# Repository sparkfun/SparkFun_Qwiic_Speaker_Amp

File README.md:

SparkFun Qwiic Speaker Amp
========================================

[*SparkFun Qwiic Speaker Amp - TPA2016D2 (DEV-20690)*](https://www.sparkfun.com/products/20690)

A Qwiic-enabled breakout board for the Texas Instruments TPA2016D2 2.8W Class-D stereo audio amp.

Repository Contents
-------------------

* **/Documentation** - Datasheets, additional product information
* **/Hardware** - Eagle design files (.brd, .sch)
  * **/Production** - Production panel files (.brd)

Documentation
--------------

* **[Installing an Arduino Library Guide](https://learn.sparkfun.com/tutorials/installing-an-arduino-library)** - Basic information on how to install an Arduino library.
* **[Library](https://github.com/sparkfun/SparkFun_TPA2016D2_Arduino_Library)** - Arduino library for the Qwiic Speaker Amp.
* **[Hookup Guide](https://learn.sparkfun.com/tutorials/2749)** - Basic hookup guide for the Qwiic Speaker Amp.

Product Versions
----------------

* **[DEV-20690](https://www.sparkfun.com/products/20690)** - Initial release

Version History
---------------
* v1.0 - Initial release

License Information
-------------------

This product is _**open source**_! 

Please review the LICENSE.md file for license information. 

If you have any questions or concerns on licensing, please contact technical support on our [SparkFun forums](https://forum.sparkfun.com/viewforum.php?f=152).

Distributed as-is; no warranty is given.

- Your friends at SparkFun.

_<COLLABORATION CREDIT>_

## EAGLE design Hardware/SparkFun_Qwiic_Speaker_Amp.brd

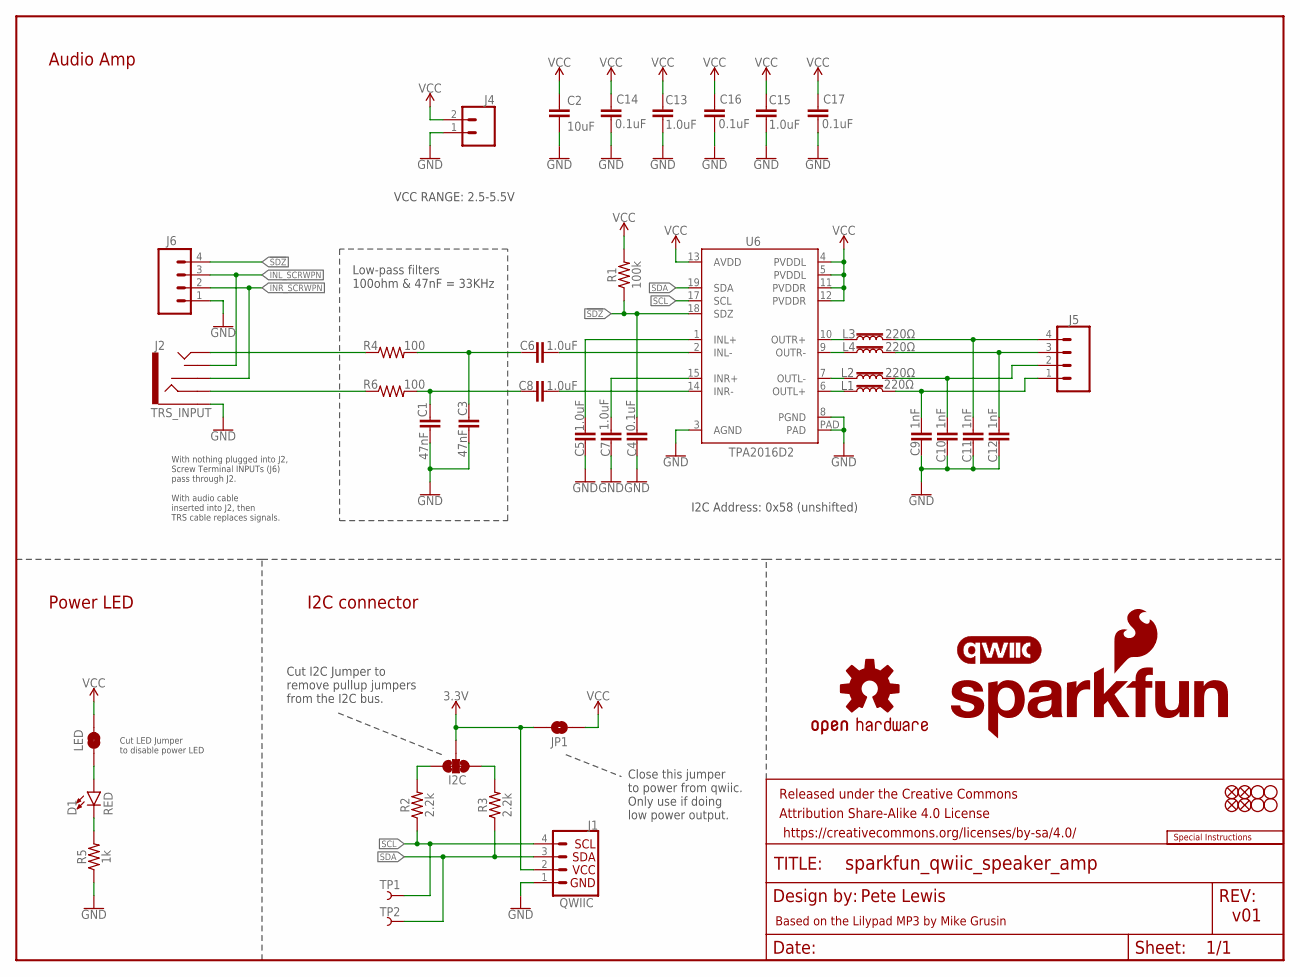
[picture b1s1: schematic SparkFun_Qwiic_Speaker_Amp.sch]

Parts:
C1, C3: 47nF; 0402-TIGHT
C2: 10uF; 0805
C4, C14, C16, C17: 0.1uF; 0402-TIGHT
C5, C6, C7, C8, C13, C15: 1.0uF; 0402-TIGHT
C9, C10, C11, C12: 1nF; 0402
D1: RED; LED-0603
FD1, FD2, FD3, FD4: FIDUCIAL1X2; FIDUCIAL-1X2
FRAME2: FRAME-LETTER; CREATIVE_COMMONS
H1, H2, H3, H4: STAND-OFFTIGHT; STAND-OFF-TIGHT
I2C: JUMPER-SMT_3_2-NC_TRACE_SILK; SMT-JUMPER_3_2-NC_TRACE_SILK
J1: QWIIC; JST04_1MM_RA
J2: TRS_INPUT; AUDIO-JACK-3.5MM-SMD
J4: CONN_023.5MM; SCREWTERMINAL-3.5MM-2
J5: CONN_04SCREW; SCREWTERMINAL-3.5MM-4
J6: SCREW; SCREWTERMINAL-3.5MM-4
JP1: JP1; SMT-JUMPER_2_NO_SILK
L1, L2, L3, L4: 220Ω; 0805
LED: JUMPER-SMT_2_NC_TRACE_SILK; SMT-JUMPER_2_NC_TRACE_SILK
LOGO2: SFE_LOGO_NAME_FLAME.1_INCH; SFE_LOGO_NAME_FLAME_.1
LOGO3: QWIIC_LOGO_4MM; QWIIC_4MM
LOGO4: OSHW-LOGOS; OSHW-LOGO-S
LOGO6: SPECIAL_INSTRUCTIONS-ORDERING; ORDERING_INSTRUCTIONS
R1: 100k; 0402-TIGHT
R2, R3: 2.2k; 0402-TIGHT
R4, R6: 100; 0402-TIGHT
R5: 1k; 0402-TIGHT
TP1, TP2: TEST-POINTTP_15TH_THRU; TP_15TH
U6: TPA2016D2; QFN-20-0.5MM

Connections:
3.3V: I2C.2, J1.2, JP1.1
!SDZ!: C4.1, J6.4, R1.1, U6.18 (SDZ)
GND: C1.2, C2.2, C3.2, C4.2, C5.1, C7.1, C9.2, C10.2, C11.2, C12.2, C13.2, C14.2, C15.2, C16.2, C17.2, J1.1, J2.SLEEVE, J4.1, J6.1, R5.1, U6.3 (AGND), U6.8 (PGND), U6.PAD
INL: J2.TIP, R4.1
INL_SCRWPN: J2.TSH, J6.3
INR: J2.RING, R6.1
INR_SCRWPN: J2.RSH, J6.2
unnamed: L1.1, U6.6 (OUTL+)
unnamed: L2.1, U6.7 (OUTL-)
unnamed: C1.1, C8.1, R6.2
unnamed: D1.C, R5.2
unnamed: C3.1, C6.1, R4.2
unnamed: D1.A, LED.1
unnamed: I2C.3, R2.2
unnamed: I2C.1, R3.2
unnamed: L3.1, U6.10 (OUTR+)
unnamed: L4.1, U6.9 (OUTR-)
unnamed: C8.2, U6.14 (INR-)
unnamed: C5.2, U6.1 (INL+)
unnamed: C6.2, U6.2 (INL-)
unnamed: C7.2, U6.15 (INR+)
SCL: J1.4, R2.1, TP1.1, U6.17 (SCL)
SDA: J1.3, R3.1, TP2.1, U6.19 (SDA)
SPK_L_+: C9.1, J5.1, L1.2
SPK_L_-: C10.1, J5.2, L2.2
SPK_R_+: C11.1, J5.4, L3.2
SPK_R_-: C12.1, J5.3, L4.2
VCC: C2.1, C13.1, C14.1, C15.1, C16.1, C17.1, J4.2, JP1.2, LED.2, R1.2, U6.4 (PVDDL), U6.5 (PVDDL), U6.11 (PVDDR), U6.12 (PVDDR), U6.13 (AVDD)

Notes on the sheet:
Pete Lewis
Audio Amp
Cut I2C Jumper to remove pullup jumpers from the I2C bus.
v01
Based on the Lilypad MP3 by Mike Grusin
Low-pass filters 100ohm & 47nF = 33KHz
With nothing plugged into J2, Screw Terminal INPUTs (J6) pass through J2. With audio cable inserted into J2, then TRS cable replaces signals.
VCC RANGE: 2.5-5.5V
Cut LED Jumper to disable power LED
Power LED
I2C connector
Close this jumper to power from qwiic. Only use if doing low power output.
I2C Address: 0x58 (unshifted)

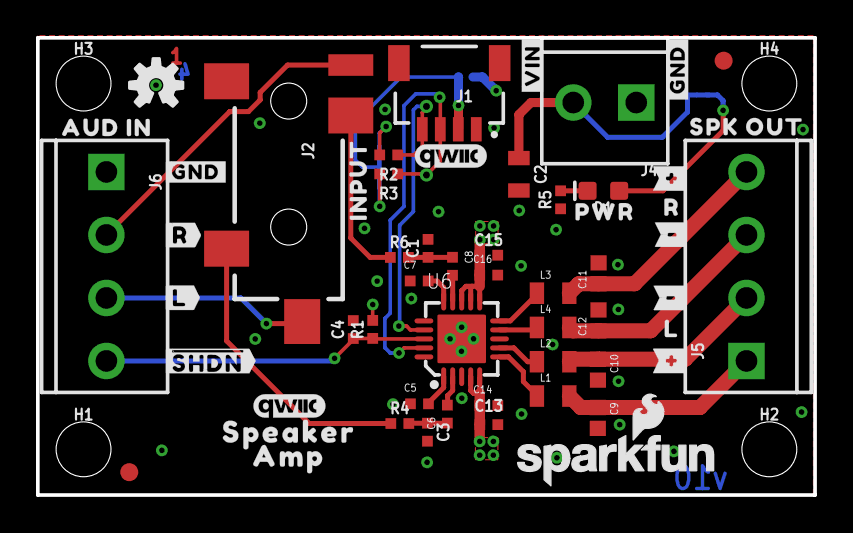
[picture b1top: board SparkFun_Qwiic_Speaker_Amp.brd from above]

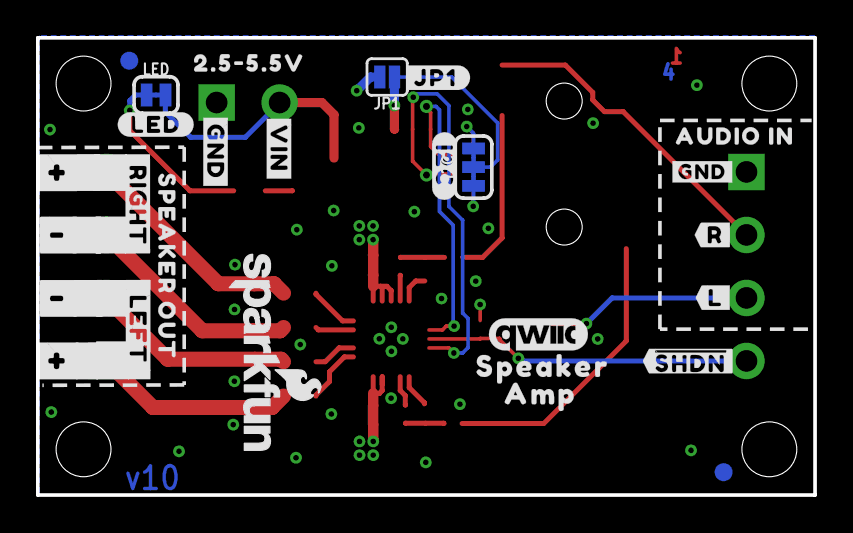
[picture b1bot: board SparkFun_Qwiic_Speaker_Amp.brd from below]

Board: 4 copper layers, 43.2 x 25.4 mm, 92 parts (27 on the bottom side), 28 nets.

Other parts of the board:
LOGO1: QWIIC_LOGO_4MM; QWIIC_4MM
U$1, U$4: SPEAKER0
U$2: #I2C#0
U$3: INPUT0
U$5: PWR26
U$6, U$8: AMP0
U$7: QWIIC_5.5MM
U$9, U$12: ###15
U$10, U$11: ###16
U$13: ##SHDN##3
U$14: R21
U$15: #VIN#24
U$16: L5
U$17: #R#11
U$18: #L#33
U$19: #L#12
U$20, U$25, U$29: #GND#25
U$21: SPK_OUT22
U$22: AUD_IN23
U$23: 2#5#5#5V24
U$24: #LED#27
U$26: #VIN#30
U$27: #GND#31
U$28: #R#34
U$30: SFE_LOGO_NAME_FLAME_.1
U$31, U$32: ###40
U$33: SPEAKER_OUT37
U$34: AUDIO_IN39
U$35, U$36: ###41
U$37: #LEFT#43
U$38: #RIGHT#44
U$39: #JP1#2
U$40: ##SHDN##2

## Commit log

2022-08-05 datasheet
2022-08-10 Initial layout getting close
2022-08-11 Layout done v01
2022-08-11 swapped inner layers to correct (2=GND, 15=VCC)
2022-08-12 schematic cleanup and minor board fixes
    -more gnd vias
    -drc approvals
2022-08-12 correcting file names to match product name
2022-08-12 Full SparkFun and flame logo on top silk
2022-08-12 moved 1/2/3/4 copper to avoid drc errors
    -adjusted trace of SCL near IC to avoid acid trap
    -rotated vias under IC to avoid being directly under where paste openings are.
2022-08-17 Added more VCC vias for connection to IC power pins.
    -also thickened up the VCC traces to IC.
    -bumped version to V10 in sch and brd
2022-08-18 increased qwiic logo size
    -fixed one wire stub
2022-08-19 production panel v10
2022-09-26 removing tpa2026d2 datasheet to avoid confusion

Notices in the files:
parts and their libraries:
SparkFun-Connectors: Licensing: Creative Commons ShareAlike 4.0 International - https://creativecommons.org/licenses/by-sa/4.0
SparkFun-Aesthetics: Released under the Creative Commons Attribution Share-Alike 4.0 License
SparkFun-Aesthetics: https://creativecommons.org/licenses/by-sa/4.0
